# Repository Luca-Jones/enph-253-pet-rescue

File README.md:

# enph-253-pet-rescue

## Overview
This project is a fully autonomous robot designed for ENPH 253 to compete in the 2025 Engineering Physics Robot Summer Competition at UBC. The cometition theme this year was Pet Rescue and goal was to drive around a course, find animal plushies in need of saving, retrieve them, and return them to the beginning of the course. Our team (team 4) of four Engineering Physics students designed and built the mechanical, electrical, and software components of this robot in 6 weeks to complete these tasks. Our team's strategy was to collect each of the pets into a basket and then lift that basket onto the zip-line to rescue them.

## Meet the Team

- [Luca Jones](https://github.com/Luca-Jones)
- [Harchetan Chohan](https://github.com/HarchetanChohan)
- [Taichi Kamei](https://github.com/Ta1k25)
- [Coen Molyneaux](https://github.com/Coen-Molyneaux)

## Mechanical Design

The mechanical design was done with Onshape as our CAD tool. It is simple to use and allows for collaboration and version control. Many different manufacturing techniques were used such as 3D printing, laser jet cutting, water jet cutting, lathing, and milling.

### Chassis

The chassis was built out of hardboard and reinforced with water-jet cut aluminium bars. This component required the most communication to perfect as every other part of the robot needs to screw into it.

### Arm

The arm and claw together were responsible for grasping each pet and placing them into the bucket in the rear. The base of the arm is attached to a lazy suzan which is bolted to the chassis, allowing it to easily rotate and pick up pets in different directions. The base also had teeth to mesh with another gear driven by a DC motor. A magnetic rotation encoder was placed underneath the base which provided the feedback needed to create a servo and set an absolute position. The arm is designed as a 4 bar linkage, allowing the servo motors that drive its vertical movement to be located at its base rather than on the hinge. The claw also uses a 4 bar linkage so that the pinsors remain parallel and reach forwards as the claw closes.

### Cascading Lift

The cascading lift mechanism was responsible for lifting the basket that stored each of the pets onto the zip line that would bring them back to the start of the course. The cascading lift works by winding a rope around a spool and extending a cabinet slider through a series of pulleys. This system proved to be extremely effective. Unlike a scissor lift, the mechanical difficulty in lifting happens near the end of the motion rather than at the beginning, allowing us to easily provide enough torque to lift our desired weight.

## Electrical Design

### H-bridge Motor Driver

### IR Sensors

### I2C Buffer and Multiplexer

### Magnetic encoder

## Software Architecture

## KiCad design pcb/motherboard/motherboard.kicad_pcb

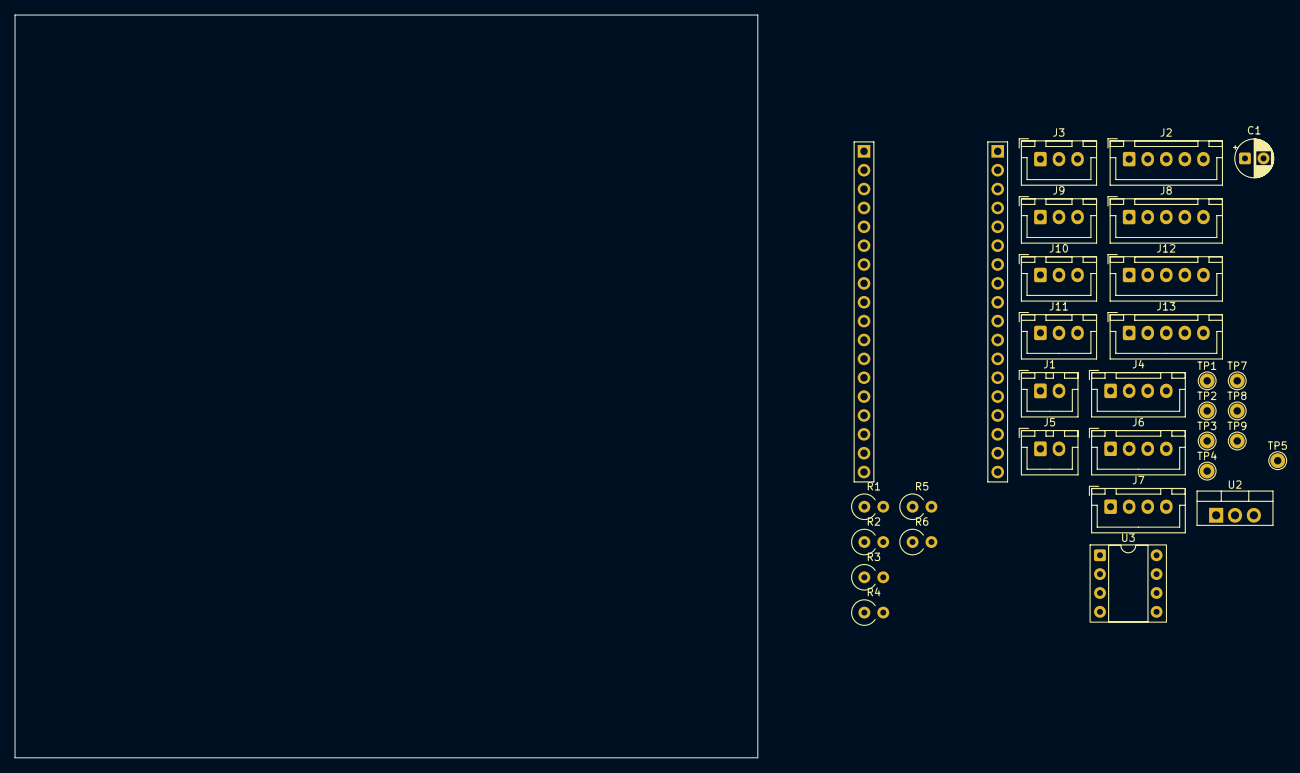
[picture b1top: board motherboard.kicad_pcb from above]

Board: 2 copper layers, 100.0 x 100.0 mm, 31 parts (0 on the bottom side), 36 nets, no tracks yet.

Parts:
C1: 0.47uF; CP_Radial_D5.0mm_P2.50mm
J1, J5: B2B-XH-A; JST_XH_B2B-XH-A_1x02_P2.50mm_Vertical
J2, J8, J12, J13: B5B-XH-A; JST_XH_B5B-XH-A_1x05_P2.50mm_Vertical
J3, J9, J10, J11: B3B-XH-A; JST_XH_B3B-XH-A_1x03_P2.50mm_Vertical
J4, J6, J7: B4B-XH-A; JST_XH_B4B-XH-A_1x04_P2.50mm_Vertical
R1, R6: 1k; R_Axial_DIN0309_L9.0mm_D3.2mm_P2.54mm_Vertical
R2, R3, R4, R5: 100k; R_Axial_DIN0309_L9.0mm_D3.2mm_P2.54mm_Vertical
TP1: GPIO1; TestPoint_THTPad_D2.0mm_Drill1.0mm
TP2: GPIO3; TestPoint_THTPad_D2.0mm_Drill1.0mm
TP3: GPIO7; TestPoint_THTPad_D2.0mm_Drill1.0mm
TP4: GPIO8; TestPoint_THTPad_D2.0mm_Drill1.0mm
TP5: GPIO20; TestPoint_THTPad_D2.0mm_Drill1.0mm
TP7: GPIO 0; TestPoint_THTPad_D2.0mm_Drill1.0mm
TP8: GPIO 39; TestPoint_THTPad_D2.0mm_Drill1.0mm
TP9: GPIO 36; TestPoint_THTPad_D2.0mm_Drill1.0mm
U1: ESP32 PICO KIT; ESP32_PICO_KIT
U2: UA9805; TO-220-3_Vertical
U3: LM311; DIP-8_W7.62mm_Socket

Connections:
+3V3: J3.3, J4.1, J6.1, J7.1, J8.1, R1.1, R6.1, U1.1 (3V3), U1.21 (3V3)
+5V: J3.1, R3.2, U1.19 (5V), U2.3 (VOUT), U3.8 (V+)
+8V: J1.1, J9.1, J10.1, J11.1, U2.1 (VIN)
/BASE GEAR MOTOR DIR: J13.2, U1.31 (32)
/BASE GEAR MOTOR PWM: J13.1, U1.30 (33)
/BIG ARM SERVO: J9.2, U1.23 (4)
/CASCADE MOTOR DIR: J13.5, U1.33 (25)
/CASCADE MOTOR PWM: J13.4, U1.32 (26)
/CLAW SERVO: J11.2, U1.25 (15(BOOT_PULLUP))
/ECHO: J4.2, U1.11 (10)
/IR1: J2.1, U1.4 (37)
/IR2: J2.2, U1.5 (38)
/IR3: J2.3, U1.6 (34)
/IR4: J2.4, U1.7 (35)
/IR5: J2.5, U1.10 (9)
/LEFT MOTOR DIR: J12.2, U1.27 (12(BOOT_PULLDOWN))
/LEFT MOTOR PWM: J12.1, U1.26 (13)
/RIGHT MOTOR DIR: J12.5, U1.29 (27)
/RIGHT MOTOR PWM: J12.4, U1.28 (14)
/SCL: J6.2, J7.2, J8.2, U1.16 (22)
/SDA: J6.3, J7.3, J8.3, U1.17 (21)
/SMALL ARM SERVO: J10.2, U1.24 (2(BOOT_PULLDOWN))
/SWITCH1: R5.1, R6.2, U1.15 (19), U3.7
/TRIG: J4.3, U1.12 (5(BOOT_PULLUP))
GND: C1.2, J1.2, J3.2, J4.4, J5.2, J6.4, J7.4, J8.4, J8.5, J9.3, J10.3, J11.3, J12.3, J13.3, R4.1, U1.2 (GND), U1.20 (GND), U1.36 (GND), U2.2 (GND), U3.1 (GND), U3.4 (V-)
unnamed: J5.1, R1.2, R2.1
unnamed: TP7.1, U1.22 (0(BOOT_PULLUP))
unnamed: TP3.1, U1.13 (7)
unnamed: TP4.1, U1.14 (8)
unnamed: TP5.1, U1.18 (20)
unnamed: TP2.1, U1.9 (RX0(GPIO3))
unnamed: TP1.1, U1.8 (TX0(GPIO1))
unnamed: TP8.1, U1.34 (VN(GPIO39))
unnamed: TP9.1, U1.35 (VP(GPIO36))
unnamed: R3.1, R4.2, R5.2, U3.2 (+)
unnamed: C1.1, R2.2, U3.3 (-)

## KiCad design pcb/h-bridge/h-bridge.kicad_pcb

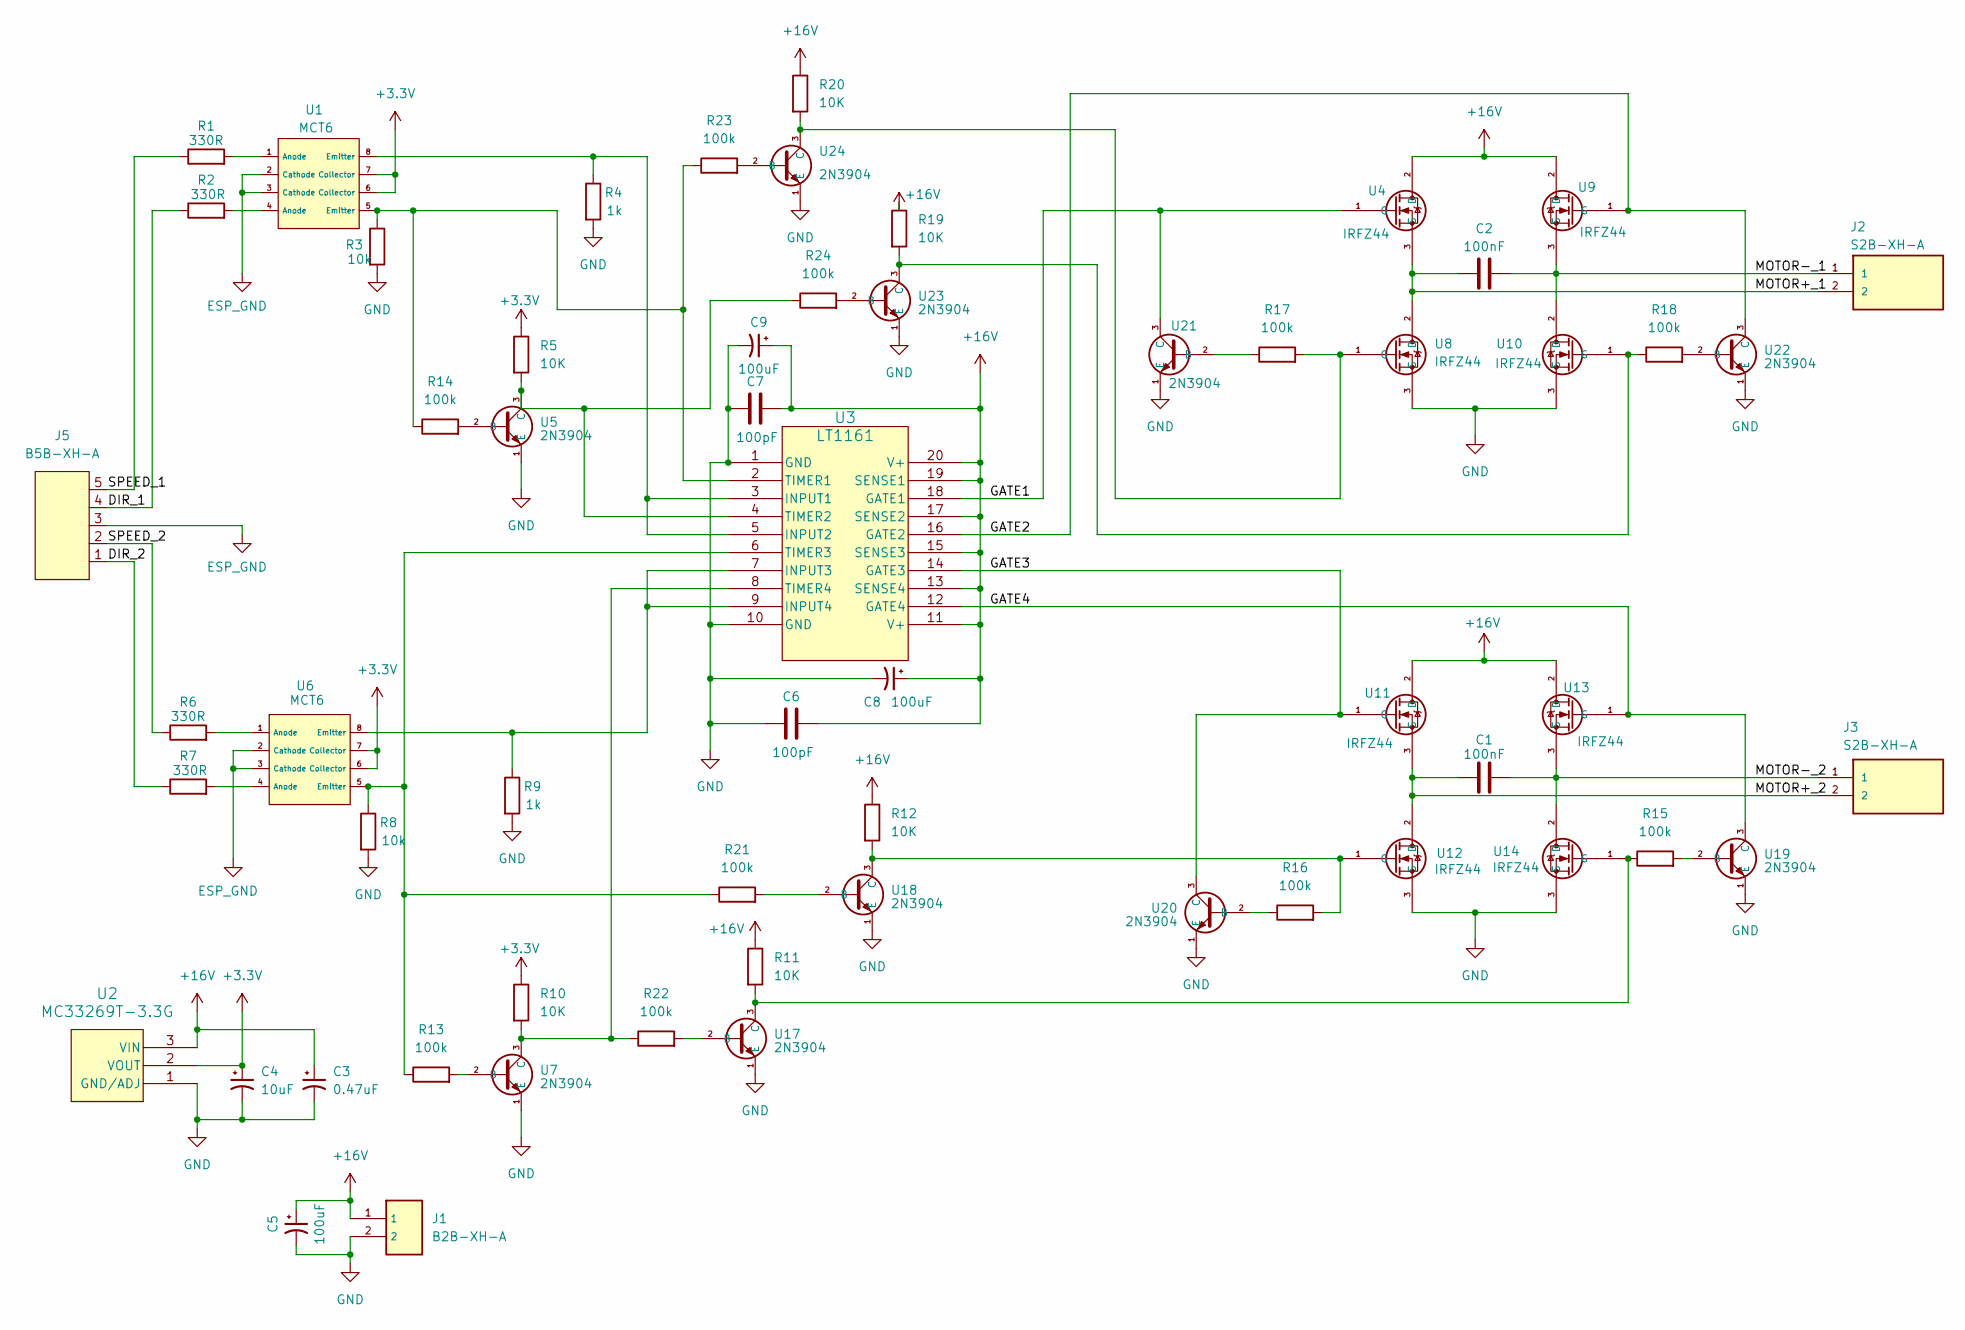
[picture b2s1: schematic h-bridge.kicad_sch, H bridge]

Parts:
C1, C2: 100nF; C_Disc_D3.0mm_W1.6mm_P2.50mm
C3: 0.47uF; CP_Radial_D5.0mm_P2.50mm
C4: 10uF; CP_Radial_D5.0mm_P2.50mm
C5, C8, C9: 100uF; CP_Radial_D6.3mm_P2.50mm
C6, C7: 100pF; C_Disc_D3.0mm_W1.6mm_P2.50mm
J1: B2B-XH-A; JST_B2B-XH-A
J2, J3: S2B-XH-A; JST_S2B-XH-A
J5: B5B-XH-A; JST_B5B-XH-A
R1, R2, R6, R7: 330R; R_Axial_DIN0309_L9.0mm_D3.2mm_P12.70mm_Horizontal
R3, R8: 10k; R_Axial_DIN0309_L9.0mm_D3.2mm_P12.70mm_Horizontal
R4, R9: 1k; R_Axial_DIN0309_L9.0mm_D3.2mm_P12.70mm_Horizontal
R5, R10, R11, R12, R19, R20: 10K; R_Axial_DIN0309_L9.0mm_D3.2mm_P12.70mm_Horizontal
R13, R14, R15, R16, R17, R18, R21, R22, R23, R24: 100k; R_Axial_DIN0411_L9.9mm_D3.6mm_P12.70mm_Horizontal
U1, U6: MCT6; DIP-8_W7.62mm_Socket
U2: MC33269T-3.3G; TO-220-3_Vertical
U3: LT1161; DIP-20_W7.62mm_Socket
U4, U8, U9, U10, U11, U12, U13, U14: IRFZ44; TO-220-3_Vertical
U5, U7, U17, U18, U19, U20, U21, U22, U23, U24: 2N3904; TO-92

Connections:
+3.3V: C4.1, R5.1, R10.1, U1.6 (Collector), U1.7 (Collector), U2.2 (VOUT), U6.6 (Collector), U6.7 (Collector)
+16V: C3.1, C5.1, C6.2, C7.2, C8.1, C9.1, J1.1, R11.1, R12.1, R19.1, R20.1, U2.3 (VIN), U3.11 (V+), U3.13 (SENSE4), U3.15 (SENSE3), U3.17 (SENSE2), U3.19 (SENSE1), U3.20 (V+), U4.2 (D), U9.2 (D), U11.2 (D), U13.2 (D)
/DIR_1: J5.4, R2.1
/DIR_2: J5.1, R7.1
/GATE1: U3.18 (GATE1), U4.1 (G), U21.3 (C)
/GATE2: U3.16 (GATE2), U9.1 (G), U22.3 (C)
/GATE3: U3.14 (GATE3), U11.1 (G), U20.3 (C)
/GATE4: U3.12 (GATE4), U13.1 (G), U19.3 (C)
/MOTOR+_1: C2.1, J2.2, U4.3 (S), U8.2 (D)
/MOTOR+_2: C1.1, J3.2, U11.3 (S), U12.2 (D)
/MOTOR-_1: C2.2, J2.1, U9.3 (S), U10.2 (D)
/MOTOR-_2: C1.2, J3.1, U13.3 (S), U14.2 (D)
/SPEED_1: J5.5, R1.1
/SPEED_2: J5.2, R6.1
ESP_GND: J5.3, U1.2 (Cathode), U1.3 (Cathode), U6.2 (Cathode), U6.3 (Cathode)
GND: C3.2, C4.2, C5.2, C6.1, C7.1, C8.2, C9.2, J1.2, R3.2, R4.2, R8.2, R9.2, U2.1 (GND/ADJ), U3.1 (GND), U3.10 (GND), U5.1 (E), U7.1 (E), U8.3 (S), U10.3 (S), U12.3 (S), U14.3 (S), U17.1 (E), U18.1 (E), U19.1 (E), U20.1 (E), U21.1 (E), U22.1 (E), U23.1 (E), U24.1 (E)
unnamed: R1.2, U1.1 (Anode)
unnamed: R2.2, U1.4 (Anode)
unnamed: R6.2, U6.1 (Anode)
unnamed: R7.2, U6.4 (Anode)
unnamed: R4.1, U1.8 (Emitter), U3.3 (INPUT1), U3.5 (INPUT2)
unnamed: R9.1, U3.7 (INPUT3), U3.9 (INPUT4), U6.8 (Emitter)
unnamed: R3.1, R14.1, R23.1, U1.5 (Emitter), U3.2 (TIMER1)
unnamed: R5.2, R24.1, U3.4 (TIMER2), U5.3 (C)
unnamed: R8.1, R13.1, R21.1, U3.6 (TIMER3), U6.5 (Emitter)
unnamed: R10.2, R22.1, U3.8 (TIMER4), U7.3 (C)
unnamed: R14.2, U5.2 (B)
unnamed: R13.2, U7.2 (B)
unnamed: R18.1, R19.2, U10.1 (G), U23.3 (C)
unnamed: R12.2, R16.2, U12.1 (G), U18.3 (C)
unnamed: R11.2, R15.1, U14.1 (G), U17.3 (C)
unnamed: R22.2, U17.2 (B)
unnamed: R21.2, U18.2 (B)
unnamed: R15.2, U19.2 (B)
unnamed: R16.1, U20.2 (B)
unnamed: R17.1, U21.2 (B)
unnamed: R18.2, U22.2 (B)
unnamed: R24.2, U23.2 (B)
unnamed: R23.2, U24.2 (B)
unnamed: R17.2, R20.2, U8.1 (G), U24.3 (C)

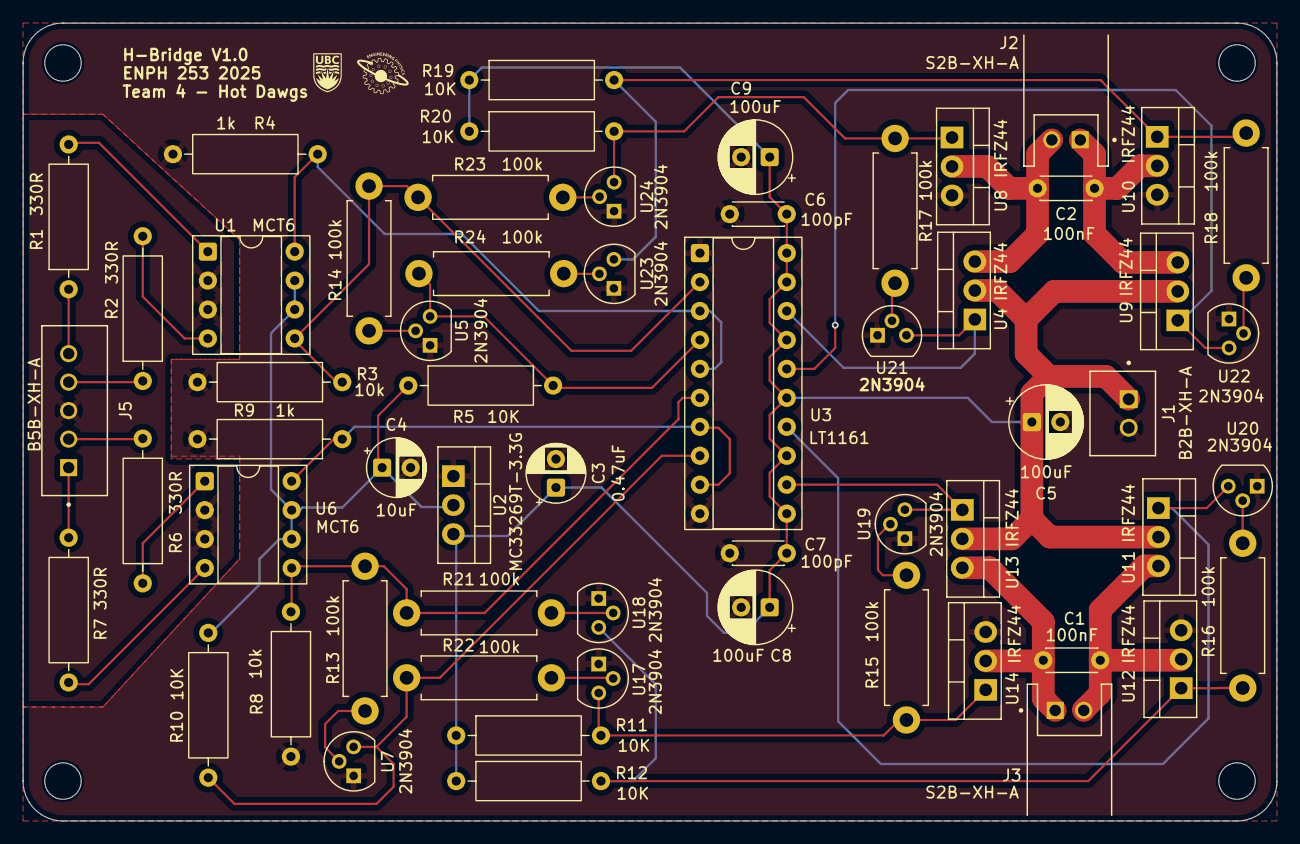
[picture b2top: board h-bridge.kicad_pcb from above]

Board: 2 copper layers, 110.0 x 70.0 mm, 59 parts (0 on the bottom side), 40 nets.

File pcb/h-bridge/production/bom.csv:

Designator,Footprint,Quantity,Value,LCSC Part #
"C1, C2",C_Disc_D4.3mm_W1.9mm_P5.00mm,2,100nF,
C3,CP_Radial_D5.0mm_P2.50mm,1,0.47uF,
C4,CP_Radial_D5.0mm_P2.50mm,1,10uF,
"C5, C8, C9",CP_Radial_D6.3mm_P2.50mm,3,100uF,
"C6, C7",C_Disc_D4.3mm_W1.9mm_P5.00mm,2,100pF,
J1,JST_B2B-XH-A,1,B2B-XH-A,
"J2, J3",JST_S2B-XH-A,2,S2B-XH-A,
J5,JST_B5B-XH-A,1,B5B-XH-A,
"R1, R2, R6, R7",R_Axial_DIN0309_L9.0mm_D3.2mm_P12.70mm_Horizontal,4,330R,
"R10, R11, R12, R19, R20, R3, R5, R8",R_Axial_DIN0309_L9.0mm_D3.2mm_P12.70mm_Horizontal,8,10K,
"R13, R14, R15, R16, R17, R18, R21, R22, R23, R24",R_Axial_DIN0411_L9.9mm_D3.6mm_P12.70mm_Horizontal,10,100k,
"R4, R9",R_Axial_DIN0309_L9.0mm_D3.2mm_P12.70mm_Horizontal,2,1k,
"U1, U6",DIP-8_W7.62mm_Socket,2,MCT6,
"U10, U11, U12, U13, U14, U4, U8, U9",TO-220-3_Vertical,8,IRFZ44,
"U17, U18, U19, U20, U21, U22, U23, U24, U5, U7",TO-92,10,2N3904,
U2,TO-220-3_Vertical,1,MC33269T-3.3G,
U3,DIP-20_W7.62mm_Socket,1,LT1161,

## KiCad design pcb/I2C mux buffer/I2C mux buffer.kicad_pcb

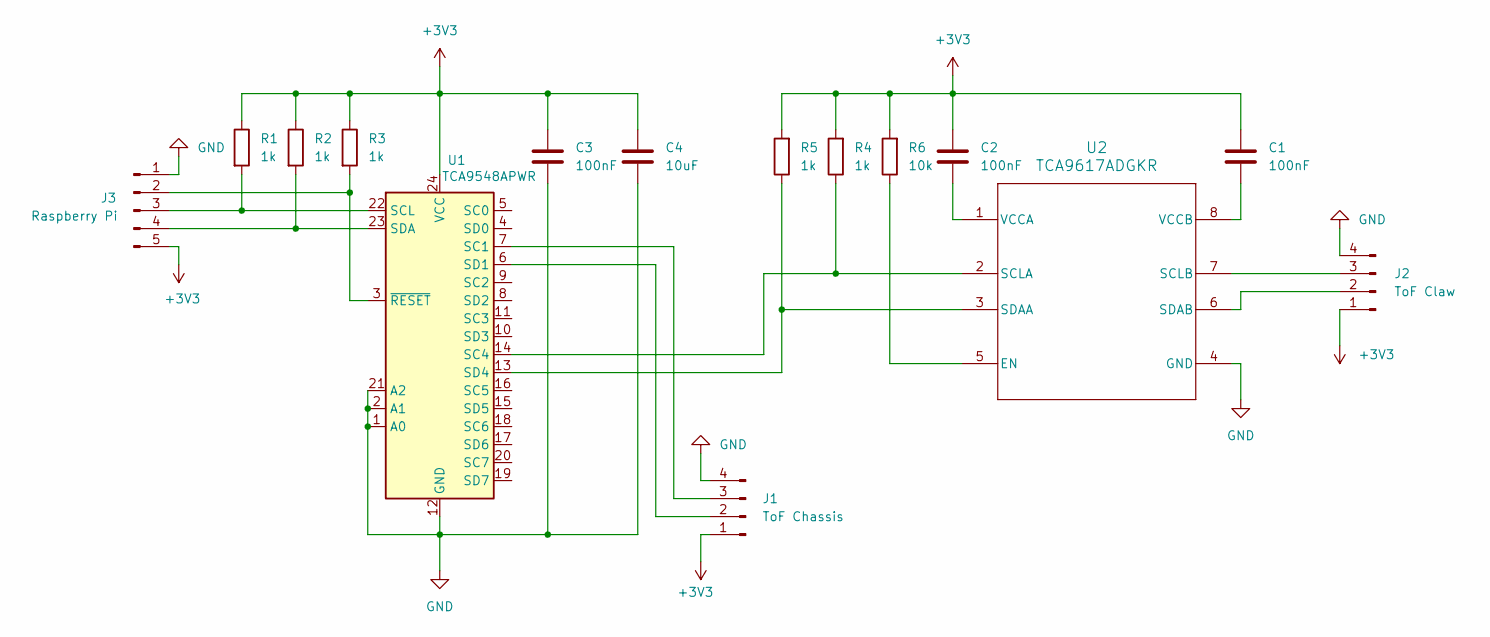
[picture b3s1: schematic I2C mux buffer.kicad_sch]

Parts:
C1, C2, C3: 100nF; C_Disc_D3.0mm_W1.6mm_P2.50mm
C4: 10uF; C_Disc_D3.0mm_W1.6mm_P2.50mm
J1: ToF Chassis; JST_EH_B4B-EH-A_1x04_P2.50mm_Vertical
J2: ToF Claw; JST_EH_B4B-EH-A_1x04_P2.50mm_Vertical
J3: Raspberry Pi; JST_PH_B5B-PH-K_1x05_P2.00mm_Vertical
R1, R2, R3, R4, R5: 1k; R_Axial_DIN0309_L9.0mm_D3.2mm_P12.70mm_Horizontal
R6: 10k; R_Axial_DIN0309_L9.0mm_D3.2mm_P12.70mm_Horizontal
U1: TCA9548APWR; TSSOP-24_4.4x7.8mm_P0.65mm
U2: TCA9617ADGKR; DGK0008A

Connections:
+3V3: C1.1, C2.1, C3.1, C4.1, J1.1, J2.1, J3.5, R1.1, R2.1, R3.1, R4.2, R5.2, R6.2, U1.24 (VCC)
GND: C3.2, C4.2, J1.4, J2.4, J3.1, U1.1 (A0), U1.2 (A1), U1.12 (GND), U1.21 (A2), U2.4 (GND)
unnamed: J1.2, U1.6 (SD1)
unnamed: J1.3, U1.7 (SC1)
unnamed: J2.2, U2.6 (SDAB)
unnamed: J2.3, U2.7 (SCLB)
unnamed: J3.2, R3.2, U1.3 (~RESET)
unnamed: J3.3, R1.2, U1.22 (SCL)
unnamed: J3.4, R2.2, U1.23 (SDA)
unnamed: R4.1, U1.14 (SC4), U2.2 (SCLA)
unnamed: R5.1, U1.13 (SD4), U2.3 (SDAA)
unnamed: R6.1, U2.5 (EN)
unnamed: C2.2, U2.1 (VCCA)
unnamed: C1.2, U2.8 (VCCB)

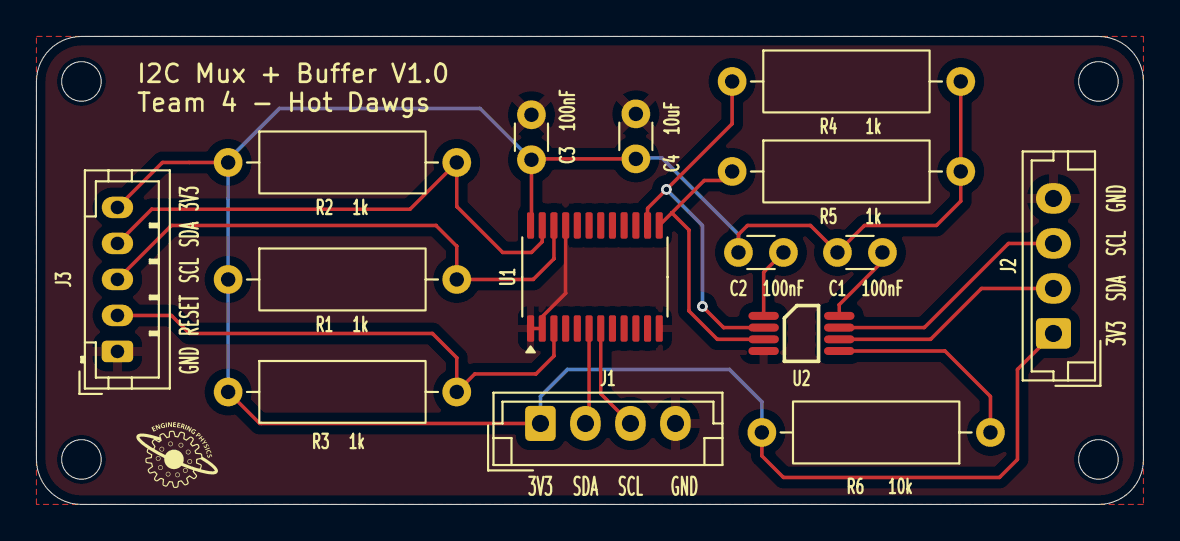
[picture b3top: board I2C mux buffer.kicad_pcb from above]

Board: 2 copper layers, 61.5 x 26.0 mm, 15 parts (0 on the bottom side), 14 nets.

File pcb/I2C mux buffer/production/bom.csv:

Designator,Footprint,Quantity,Value,LCSC Part #
"C1, C2, C3",C_Disc_D3.0mm_W1.6mm_P2.50mm,3,100nF,
C4,C_Disc_D3.0mm_W1.6mm_P2.50mm,1,10uF,
J1,JST_EH_B4B-EH-A_1x04_P2.50mm_Vertical,1,ToF Chassis,
J2,JST_EH_B4B-EH-A_1x04_P2.50mm_Vertical,1,ToF Claw,
J3,JST_PH_B5B-PH-K_1x05_P2.00mm_Vertical,1,Raspberry Pi,
"R1, R2, R3, R4, R5",R_Axial_DIN0309_L9.0mm_D3.2mm_P12.70mm_Horizontal,5,1k,
R6,R_Axial_DIN0309_L9.0mm_D3.2mm_P12.70mm_Horizontal,1,10k,
U1,TSSOP-24_4.4x7.8mm_P0.65mm,1,TCA9548APWR,
U2,DGK0008A,1,TCA9617ADGKR,

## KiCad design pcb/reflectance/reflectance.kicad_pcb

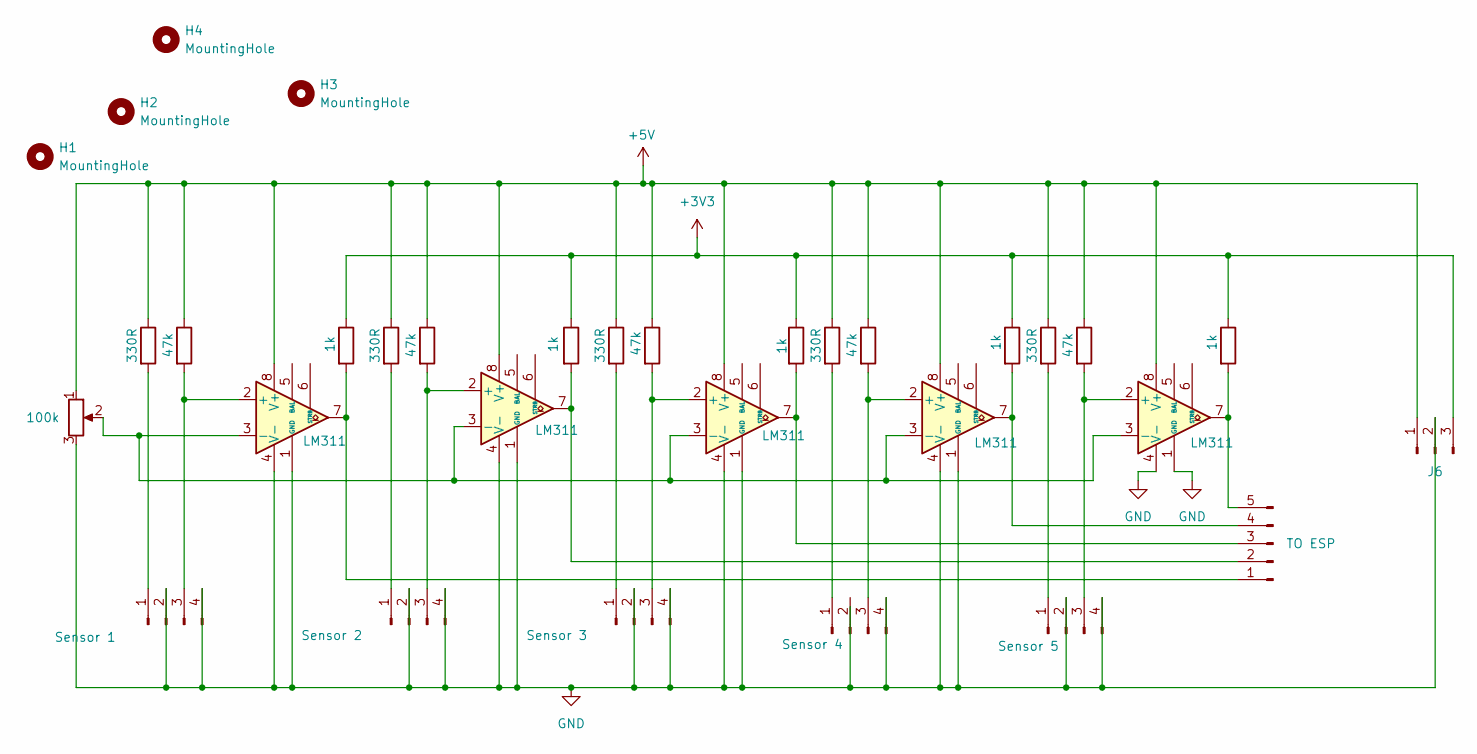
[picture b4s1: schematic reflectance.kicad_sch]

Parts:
H1, H2, H3, H4: MountingHole; MountingHole_3.2mm_M3
J1, J3: JCT 4pin; JST_EH_B4B-EH-A_1x04_P2.50mm_Vertical
J2: JCt 4pin; JST_EH_B4B-EH-A_1x04_P2.50mm_Vertical
J4, J7: Reflectance Sensor 4; JST_EH_B4B-EH-A_1x04_P2.50mm_Vertical
J6: Conn_01x03_Pin; JST_EH_B3B-EH-A_1x03_P2.50mm_Vertical
J8: Conn_01x05_Pin; JST_EH_B5B-EH-A_1x05_P2.50mm_Vertical
R1, R4, R7, R10, R15: 47k; R_Axial_DIN0207_L6.3mm_D2.5mm_P7.62mm_Horizontal
R2, R5, R8, R11, R14: 330R; R_Axial_DIN0207_L6.3mm_D2.5mm_P7.62mm_Horizontal
R3, R6, R9, R12, R16: 1k; R_Axial_DIN0207_L6.3mm_D2.5mm_P7.62mm_Horizontal
RV1: 100k; Potentiometer_Bourns_3296W_Vertical
U1, U2, U3, U4, U5: LM311; DIP-8_W7.62mm_Socket_LongPads

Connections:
+3V3: J6.3, R3.1, R6.1, R9.1, R12.1, R16.1
+5V: J6.1, R1.1, R2.1, R4.1, R5.1, R7.1, R8.1, R10.1, R11.1, R14.1, R15.1, RV1.1, U1.8 (V+), U2.8 (V+), U3.8 (V+), U4.8 (V+), U5.8 (V+)
GND: J1.2, J1.4, J2.2, J2.4, J3.2, J3.4, J4.4, J6.2, J7.2, J7.4, RV1.3, U1.1 (GND), U1.4 (V-), U2.1 (GND), U2.4 (V-), U3.1 (GND), U3.4 (V-), U4.1 (GND), U4.4 (V-), U5.1 (GND), U5.4 (V-)
unnamed: J1.1, R2.2
unnamed: J1.3, R1.2, U2.2 (+)
unnamed: J2.1, R5.2
unnamed: J2.3, R4.2, U1.2 (+)
unnamed: J3.1, R8.2
unnamed: J3.3, R7.2, U3.2 (+)
unnamed: J4.1, R11.2
unnamed: J4.3, R10.2, U4.2 (+)
unnamed: J7.1, R14.2
unnamed: J7.3, R15.2, U5.2 (+)
unnamed: J8.1, R3.2, U2.7
unnamed: J8.2, R6.2, U1.7
unnamed: J8.3, R9.2, U3.7
unnamed: J8.4, R12.2, U4.7
unnamed: J8.5, R16.2, U5.7
unnamed: RV1.2, U1.3 (-), U2.3 (-), U3.3 (-), U4.3 (-), U5.3 (-)

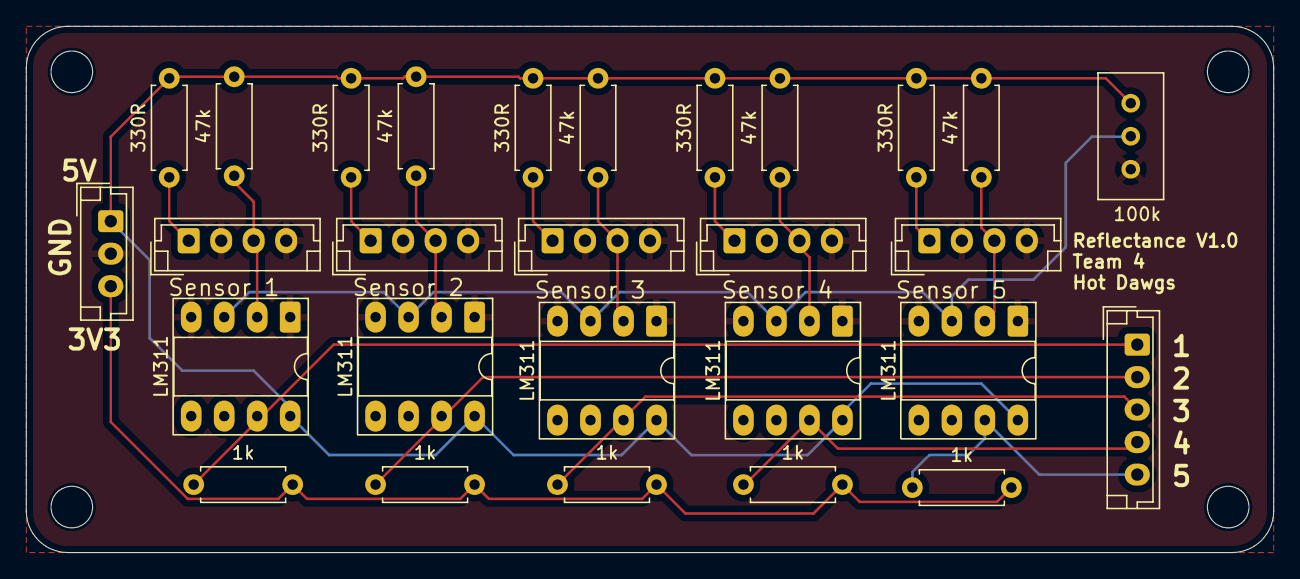
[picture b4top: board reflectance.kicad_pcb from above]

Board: 2 copper layers, 96.0 x 40.5 mm, 32 parts (0 on the bottom side), 19 nets.

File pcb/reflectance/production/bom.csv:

Designator,Footprint,Quantity,Value,LCSC Part #
"J1, J2, J3",JST_EH_B4B-EH-A_1x04_P2.50mm_Vertical,3,JCT 4pin,
"J4, J7",JST_EH_B4B-EH-A_1x04_P2.50mm_Vertical,2,Reflectance Sensor 4,
J6,JST_EH_B3B-EH-A_1x03_P2.50mm_Vertical,1,Conn_01x03_Pin,
J8,JST_EH_B5B-EH-A_1x05_P2.50mm_Vertical,1,Conn_01x05_Pin,
"R1, R10, R15, R4, R7",R_Axial_DIN0207_L6.3mm_D2.5mm_P7.62mm_Horizontal,5,47k,
"R11, R14, R2, R5, R8",R_Axial_DIN0207_L6.3mm_D2.5mm_P7.62mm_Horizontal,5,330R,
"R12, R16, R3, R6, R9",R_Axial_DIN0207_L6.3mm_D2.5mm_P7.62mm_Horizontal,5,1k,
RV1,Potentiometer_Bourns_3296W_Vertical,1,100k,
"U1, U2, U3, U4, U5",DIP-8_W7.62mm_Socket_LongPads,5,LM311,

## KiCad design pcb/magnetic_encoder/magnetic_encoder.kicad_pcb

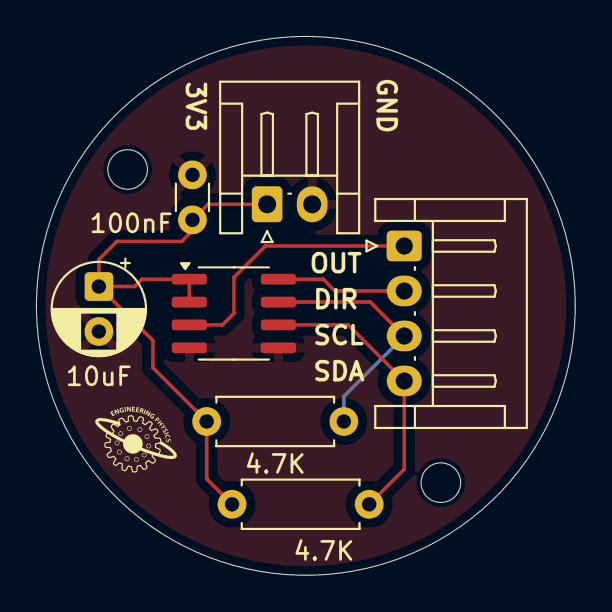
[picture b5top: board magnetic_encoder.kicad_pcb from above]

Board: 2 copper layers, 29.9 x 29.9 mm, 9 parts (0 on the bottom side), 6 nets.

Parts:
C1: 100nF; C_Disc_D3.0mm_W1.6mm_P2.50mm
C2: 10uF; CP_Radial_D5.0mm_P2.50mm
H1, H3: MountingHole; MountingHole_2.2mm_M2
J1: Conn_01x02_Pin; JST_EH_S2B-EH_1x02_P2.50mm_Horizontal
J2: Conn_01x04_Pin; JST_EH_S4B-EH_1x04_P2.50mm_Horizontal
R1, R2: 4.7K; R_Axial_DIN0207_L6.3mm_D2.5mm_P7.62mm_Horizontal
U1: SOIC-8_3.9x4.9mm_P1.27mm

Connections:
+3.3V: C1.1, C2.1, J1.1, R1.1, R2.1, U1.1 (VDD5V), U1.2 (VDD3V3)
GND: C1.2, C2.2, J1.2, U1.4 (GND), U1.5 (PGO)
unnamed: J2.1, U1.3 (OUT)
unnamed: J2.2, U1.8 (DIR)
unnamed: J2.3, R2.2, U1.7 (SCL)
unnamed: J2.4, R1.2, U1.6 (SDA)

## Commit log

2025-06-20 tof added
2025-06-28 width test
2025-06-28 hello
2025-06-28 Working pillar detection
2025-06-28 improved groundpet detection
2025-07-05 Servo library v1 written for the claw
2025-07-11 added pcb dir
2025-07-11 I2C Mux Bufffer
2025-07-11 pcbs
2025-07-12 pcbs reviewed
2025-07-12 expanded h-bridge ground plane
2025-07-12 h-bridge final export
2025-07-13 attempted calibration of the arm
2025-07-13 first state machine template
2025-07-14 modified state machine template
2025-07-14 expanded template to cover all states
2025-07-15 arm moves nicely now
2025-07-15 template code for the ToF test on the pi
2025-07-15 added uart messaging into ToF python code
2025-07-15 arm ready to move after tof is tested
2025-07-15 Updated pid code with wifi tuning
2025-07-16 new servo tested. Note that the ToF python in this branch is wrong
2025-07-16 sonar works quite well for edge detection
2025-07-16 changed to .cpp files for debugging with oled, extended boiler plate code, fixed header guard issue
2025-07-16 even more boiler plate
2025-07-16 added logging functions for states and events
2025-07-17 highly simplified the state machine template, also now I know that it compiles
2025-07-18 first working button press state machine with a timed return
2025-07-18 tof codes on esp
2025-07-18 tof library imported
2025-07-18 pet on ground works
2025-07-18 modified ToF
2025-07-18 legible
2025-07-18 tof code added, but it does not seems to run as well as the original
2025-07-18 commit ToF
2025-07-18 getDistanceToObject works
2025-07-18 changed mean calc
2025-07-19 fixed some issues
2025-07-19 the magnetic encoder works!
2025-07-20 sensors and actuators header files sorted out
2025-07-20 refactored actuators and sensors, all compiles
2025-07-20 refactored state machine header and cpp file and added many TODO's
2025-07-20 moved all headers to include, compiles
2025-07-20 included all of the states needed, may reduce this number
2025-07-20 organized states and have 7 of them now
2025-07-20 I had forgotten to add the transitions and upate the events enum
2025-07-21 partially integrated a second ToF
2025-07-21 ToF integrated
2025-07-21 finished state store
2025-07-21 implemented the magnetic encoder
2025-07-21 sonar implemented
2025-07-21 magnetic encoder implemented as pid, still needs to be tested and tuned
2025-07-21 implemented the return pets state, and fixed the direction issue with the base gear
2025-07-21 implemented reaching state
2025-07-21 implemented claw and retreat strategy
2025-07-21 implemented tape following state and fixed a bit masking issue in the mag encoder code
2025-07-21 forgot to make sure it compiles
2025-07-22 mux code
2025-07-23 updates pin-out and removed the rotary encoder and start button
2025-07-23 removed .DS_Store files
2025-07-24 tests implemented
2025-07-24 pin out updated to reflect mounted motors
2025-07-26 TIME TRIALS
2025-07-27 added zip files to .gitignore
2025-07-27 schematic and footprints finished
2025-07-27 more schematics going to happen
2025-07-28 motherboard
2025-07-28 actuator classes fully implemented, TODOs added
2025-07-29 actuators and sensors finished and tests compile
2025-07-29 implemented tof detection from time trials testing into the state machine
2025-07-30 state machine ready to test
2025-07-31 sonar and cascade tests ran
2025-08-01 mag ok, base gear tuned
2025-08-02 tof sensing works quite well, tape following state to be tested
2025-08-03 tape following works, added ramp drop off startegy
2025-08-03 tested hardware timer
2025-08-04 state machine tof lag is an issue
2025-08-04 commit with millis
2025-08-04 tof task on second core
2025-08-04 RTOS tasks test / experiment added
2025-08-04 fixed mutex bugs
2025-08-04 fixed base gear pid
2025-08-05 the culprit is the display, to be removed
2025-08-05 tof algorithm needs modification, but crashing no longer an issue
2025-08-05 pup break to be tested
2025-08-05 tuesday aug 5 3pm
2025-08-05 right pet detected
2025-08-06 can pick up a pet and put it in the basket!
2025-08-06 arm in bucket start, tweaking needed for the tof, and consider the wall
2025-08-06 bucket lifts
2025-08-07 first pet!
2025-08-07 boosted base speed to 70
2025-08-07 running over debris strategy
2025-08-07 base gear issue resolved: pwm frequency too high
2025-08-07 changing the pwm freq messes with the tape following, scrambling the channels fixes itgit commit
2025-08-07 pwm channel to timers configured correctly
2025-08-07 first run 2 assisted
2025-08-07 3 assisted pets run
2025-08-07 something is crashing....
2025-08-07 FINAL COMPETITION CODE
2025-09-02 first edit to the README and moving deprecated directories
2025-09-02 all depricated code moved to depricated/
